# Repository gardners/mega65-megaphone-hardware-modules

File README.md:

# megaphone-r5-modular
Modularised MEGAphone Design

This project is being carried out with the support of the NLnet Foundation under: https://nlnet.nl/project/MEGA65-MVP/

The goal of this project is to push the MEGAphone forward towards a Minimum Viable Product (MVP) in a cost-effective way by modularising the PCB
allowing for faster development and lower development costs as a result. Also, the modularisation helps to work around supply-chain problems by
allowing the replacement of hard to source components, without requiring a full PCB redesign.  Those modules can also be manufactured much more easily
in a domestic setting, as there is less cumulative chance of messing something up.  Alternatively, they can be manufactured in modest sized batches
using PCB fabrication places like PCBWay, who also offer an assembly option.

The following sections outline the tasks and their current state of progress, where appropriate.

## Task 1: Development and testing of core simple cellular telephony and text messaging software

The software aspect of this project relates to the software required to control and interact with the hardware modules, as well as to perform basic telephony functionality.

## Task 2: Modularisation and testing of the PCB design

The major hardware stream of this project is focused on modularising the MEGAphone PCB, so that the modules can be iterated and/or manufactured independently. This is to support both users self-manufacturing, so that the complexity of the fabrication process can be greatly simplified, as well as to allow for much faster and, including ad-hoc response to future supply chain challenges. 

### 2.1 High-efficiency DC-DC converter module to power the various sub-systems

High-current and high-efficiency modules are required for the main FPGA, cellular modem, auxilliary communications module, LCD panel, and external speaker/bluetooth modules.  It is desirable to come up with a single module that can be reused several times for these purposes.  The cellular modems are likely to be the highest draw item, and according to https://ww1.microchip.com/downloads/en/Appnotes/ANLPS300-APID.pdf, they can draw upto around 2A at 3.3V, which is the voltage we will most likely use, since it allows a common voltage for many of our sub-systems.

It is unlikely that any other device on the system will consume more power than this, so our DC-DC modules need to support 2A.

A further requirement is that it must be buck-boost, as the LiFePO4 cells can go below 3.3V, but when charged are >3.3V.

Some possible parts to consider:

STBBJ3 https://www.st.com/en/power-management/stbb3j.html  (2A in buck mode, i.e., where VIN > 3.3V, but only 800mA in boost mode, i.e., where VIN < 3.3V). 5x4 grid array, without thermal pad. Shutdown and soft-start. "typical" efficiency of 94%
LTC3113 https://www.analog.com/media/en/technical-documentation/data-sheets/3113f.pdf (3A in buck mode, 1.5A in boost mode). "up to" 96% efficiency. Choice of grid array and TSSOP -- but with a concealled thermal pad on the underside, which is not easy to hand-solder. AU$20 each for TTSOP!

### 2.2 Low-energy power-management module to minimise energy consumption of device, especially in low-power modes

### 2.3 Battery management and energy harvesting module to allow USB-C, integrated solar panel and external 12/24V vehicle battery power sources, and efficient management of the integrated rechargeable battery

### 2.4 Cellular modem communications module, including SIM card module

### 2.5 Internal microphone and speaker module

### 2.6 External speaker and bluetooth headset interface module

### 2.7 Primary FPGA carrier module, leveraging off-the-shelf FPGA modules if at all possible

### 2.8 LCD panel interface module

### 2.9 Auxiliary communications module, e.g., LoRa, ultra-sonic, infra-red or mm wave

Low-cost LoRa devices based on the SX1262 look to be an option, using open-source software like this: https://github.com/beegee-tokyo/SX126x-Mesh-Network
The goal would be for the module to be able to autonomously participate in the mesh while the main process is off.  ESP32s can go into low power modes with <1mA consumption according to https://www.arrow.com/en/research-and-events/articles/esp32-power-consumption-can-be-reduced-with-sleep-modes, and the SX1262 uses only about 5mA to listen for packets, and perhaps 70mA when active, so this looks plausible. The SX1262 when transmitting can draw upto about 120mA according to https://semtech.my.salesforce.com/sfc/p/#E0000000JelG/a/2R000000Un7F/yT.fKdAr9ZAo3cJLc4F2cBdUsMftpT2vsOICP7NmvMo

Thus the total power consumption of an auxilliary communications module (assuming we include an ESP32 in it, rather than using the power management FPGA to run the mesh) will be about 5mA while idle (~17mW) and upto ~200mA (~660mW).

### 2.10 Main carrier board and assembly, into which the various modules connect

## Task 3: Integration, Integration testing and remediation of the modules

Once the modules have been tested independently, this activity is focussed on testing the behaviour of the modules when connected to one another, including any VHDL/FPGA programming required to achieve this.

### 3.1 Requirements specification and analysis

### 3.2 Hardware integration and testing, including FPGA programming

### 3.3 Software integration and testing

### 3.4 Engage with and respond to security and accessibility audits

### 3.5 Remediation and contingency – for addressing any issues with the software and/or hardware components identified during the integration, and implementing or documenting appropriate solutions and/or work-arounds as appropriate

## Task 4: Preparation of Prototype Units

This activity focuses on taking the integrated hardware and software modules, and building a small number of units that are alpha-quality prototypes.  The specific objective is that they be integrated into units that are suitable for developers to use to continue development of both hardware and software of the system.  These units may be somewhat larger than the final obtainable footprint, depending on the costs of designing and fabricating the housings/enclosures.  The limited budget prevents the engagement of industrial designers who would be required for the completion of design for manufacture. Instead, we anticipate that the enclosures will be relatively simple 3D printed designs.
The remediation budget line is to allow for adjustment to the case design, the fabricated case and/or any of the hardware modules, so that the prototypes can be assembled and be as functional as possible.

### 4.1 Case Design

### 4.2 Case Fabrication

### 4.3 Assembly

### 4.4 Remediation / Mitigation, e.g., of any fitment issues, whether by adjustment of the case, reworking of a module or other means.

Status of the modules 

| Milestone | Module | Reqs | Sch | Layout | Fab | Assembly | Test | Revision |
| --- | --- | --- | --- | --- | --- | --- | --- | --- |
| 2.1 | [High Efficieny DC-DC Converter](modules/high-efficiency_dc-dc_converter) | Y | Y | Y | Y | N | N | N |
| 2.2 | [Low-Enery Power Management Module]() | Y | Y | Y | Y | N | N | N |
| 2.3 | [Battery Management / Solar / Charge Module](modules/mppt-charge-controller) | Y | Y | Y | Y | N | N | N |
| 2.4 | [Cellular Modem Comms Module](modules/cellular-modem) | Y | Y | Y | Y | Y | Y | Y |
| 2.4 | [SIM Card Carrier](modules/sim-and-sd-card) | Y | Y | Y | Y | Y | Y | Y |
| 2.5 | [Internal microphone](modules/mems-microphone) | Y | N | N | N | N | N | N |
| 2.5 | [Internal speaker]() | Y | N | N | N | N | N | N |
| 2.6 | [External speaker]() | Y | Y | Y | Y | N | N | N |
| 2.6 | [Bluetooth headset interface](modules/bluetooth) | Y | N | N | N | N | N | N |
| 2.7 | [Primary FPGA carrier](modules/te0725-carrier) | Y | Y | Y | Y | N | N | N |
| 2.8 | [LCD Panel Interface](modules/lcd-panel) | Y | N | N | N | N | N | N |
| 2.9 | [Aux Comms]() | Y | N | N | N | N | N | N |
| 2.10 | [Main Carrier Board]() | Y | N | N | N | N | N | N |

### Assembled modules

First batch

LCD 

DC/DC

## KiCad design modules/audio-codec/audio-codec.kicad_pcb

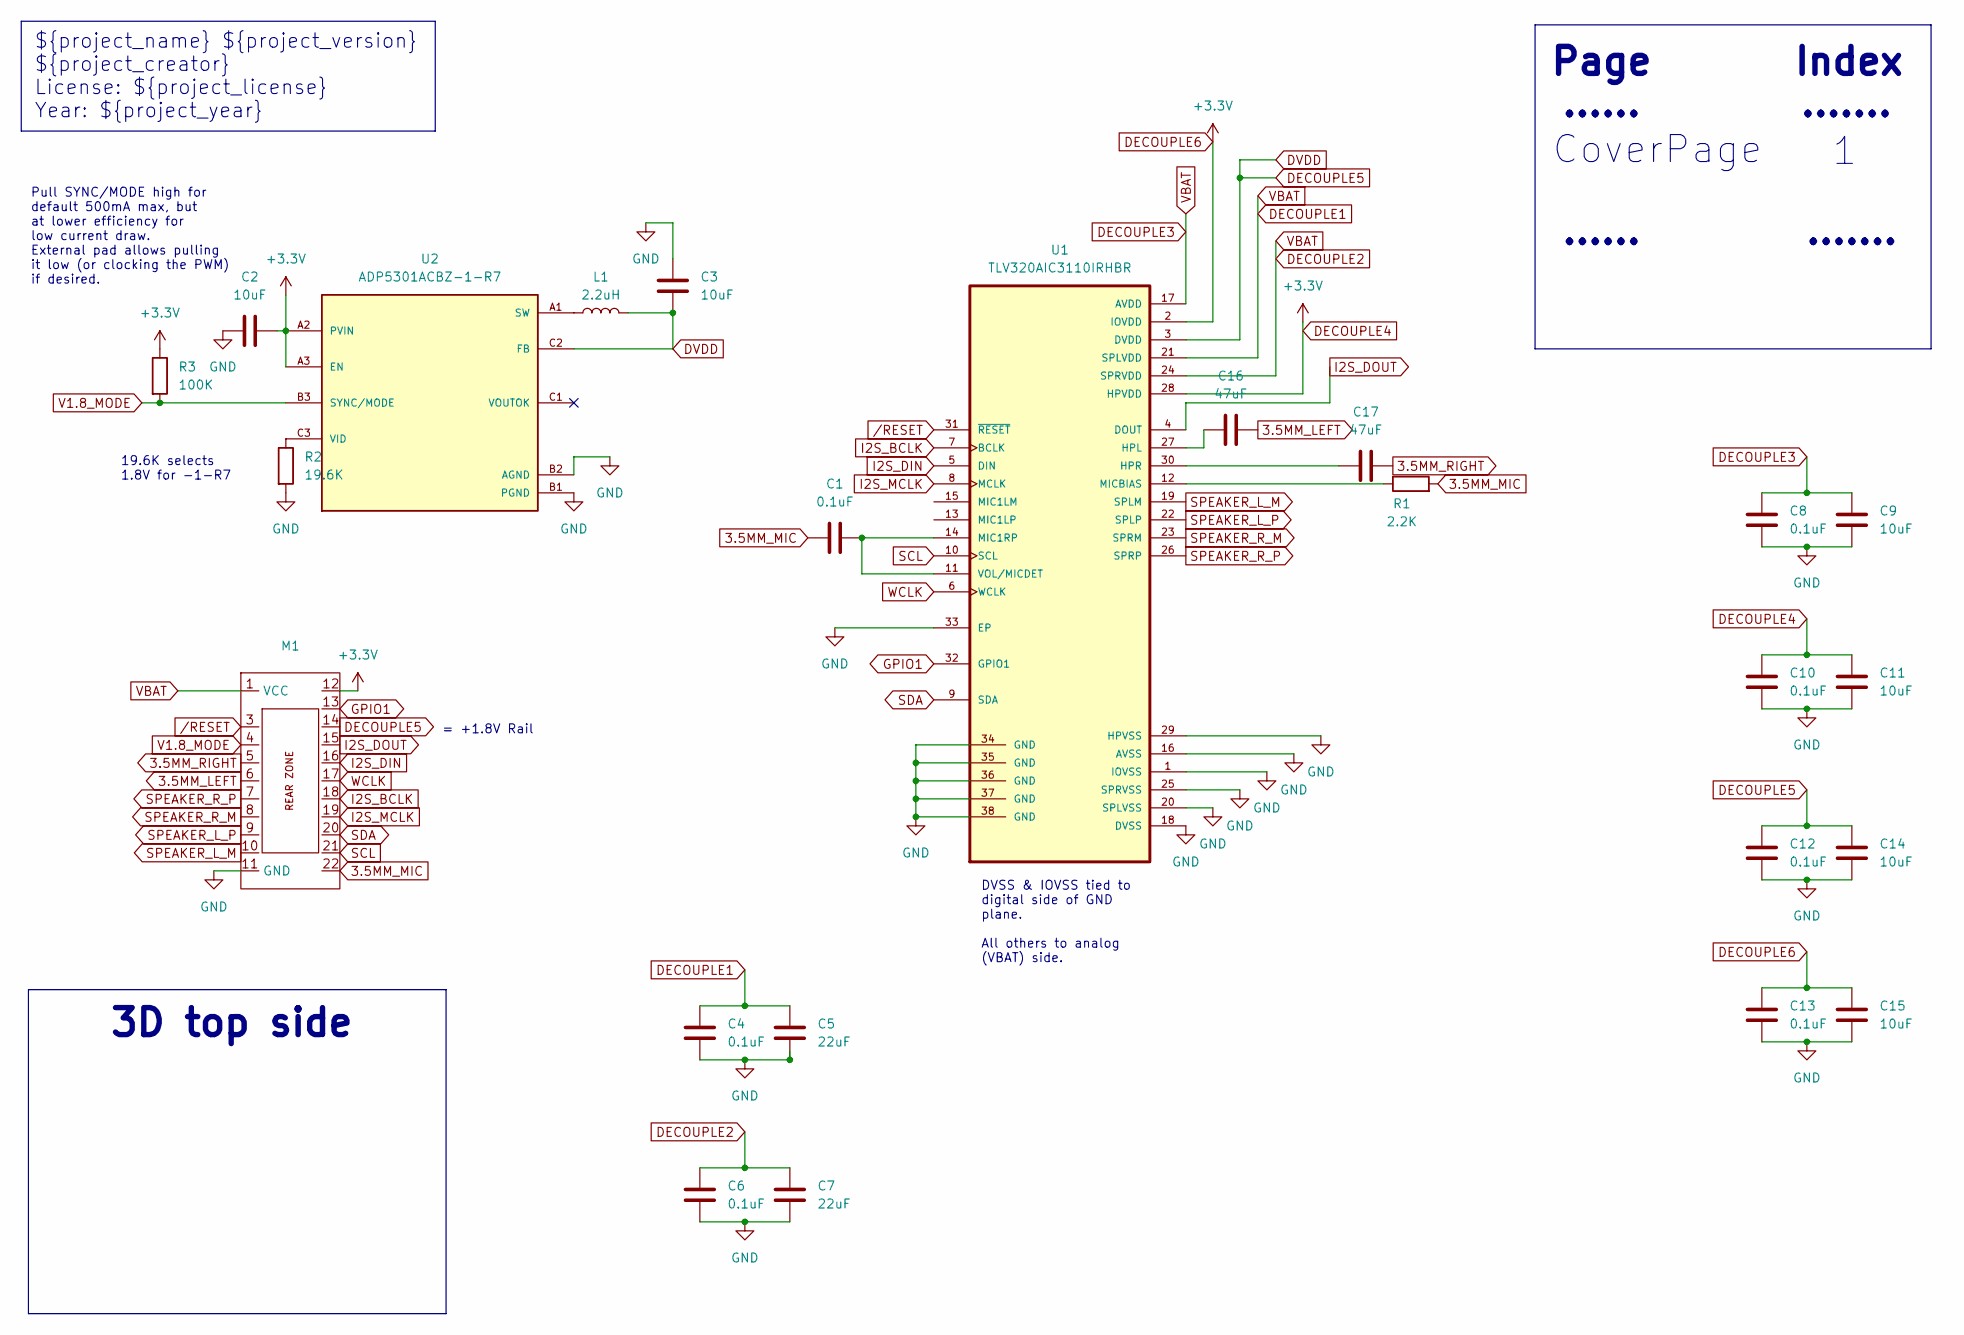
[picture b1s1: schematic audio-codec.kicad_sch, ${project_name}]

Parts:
C1, C4, C6, C8, C10, C12, C13: 0.1uF; C_0603_1608Metric; Mfr. PN C0603C104M4RAC; Mouser PN 80-C0603C104M4RAC
C2, C3, C9, C11, C14, C15: 10uF; C_0603_1608Metric; Mfr. PN C0603C106M9PAC7411; Mouser PN 80-C0603C106M9P7411
C5, C7: 22uF; C_0603_1608Metric; Mfr. PN CC0603MRX5R5BB226; Mouser PN 603-CC603MRX5R5BB226
C16, C17: 47uF; C_0603_1608Metric; Mfr. PN GRM188R60E476ME15J; Mouser PN 81-GRM188R60E476ME5J
L1: 2.2uH; L_0805_2012Metric; Mouser PN 810-MLP2016V2R2MT0S1
M1: MegaCastle2x11-Module-I22.0x23.1-MBFFFFC-SPAREPAD
R1: 2.2K; R_0603_1608Metric; Mfr. PN RT0603DRE072K2L; Mouser PN 603-RT0603DRE072K2L
R2: 19.6K; R_0603_1608Metric; Mouser PN 603-RT0603BRD0719K6L
R3: 100K; R_0603_1608Metric; Mouser PN 603-RC0603FR-07100KL
U1: TLV320AIC3110IRHBR; IC_ADS125H01IRHBT; Mouser PN 595-V320AIC3110IRHBR
U2: ADP5301ACBZ-1-R7; BGA9C50P3X3_187X165X66N; Mouser PN 584-ADP5301ACBZ-1-R7

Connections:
3.5MM_LEFT: C16.2, M1.6
3.5MM_MIC: C1.2, M1.22, R1.2
3.5MM_RIGHT: C17.2, M1.5
DECOUPLE1: C4.1, C5.1, C6.1, C7.1, C8.1, C9.1, M1.1 (VCC), U1.17 (AVDD), U1.21 (SPLVDD), U1.24 (SPRVDD)
DECOUPLE4: C2.2, C10.1, C11.1, C13.1, C15.1, M1.12, R3.1, U1.2 (IOVDD), U1.28 (HPVDD), U2.A2 (PVIN), U2.A3 (EN)
DECOUPLE5: C3.1, C12.1, C14.1, L1.2, M1.14, U1.3 (DVDD), U2.C2 (FB)
GND: C2.1, C3.2, C4.2, C5.2, C6.2, C7.2, C8.2, C9.2, C10.2, C11.2, C12.2, C13.2, C14.2, C15.2, M1.11 (GND), R2.2, U1.1 (IOVSS), U1.16 (AVSS), U1.18 (DVSS), U1.20 (SPLVSS), U1.25 (SPRVSS), U1.29 (HPVSS), U1.33 (EP), U1.34 (GND), U1.35 (GND), U1.36 (GND), U1.37 (GND), U1.38 (GND), U2.B1 (PGND), U2.B2 (AGND)
GPIO1: M1.13, U1.32 (GPIO1)
I2S_BCLK: M1.18, U1.7 (BCLK)
I2S_DIN: M1.16, U1.5 (DIN)
I2S_DOUT: M1.15, U1.4 (DOUT)
I2S_MCLK: M1.19, U1.8 (MCLK)
unnamed: C16.1, U1.27 (HPL)
unnamed: C17.1, U1.30 (HPR)
unnamed: C1.1, U1.11 (VOL/MICDET), U1.14 (MIC1RP)
unnamed: R1.1, U1.12 (MICBIAS)
unnamed: L1.1, U2.A1 (SW)
unnamed: R2.1, U2.C3 (VID)
SCL: M1.21, U1.10 (SCL)
SDA: M1.20, U1.9 (SDA)
SPEAKER_L_M: M1.10, U1.19 (SPLM)
SPEAKER_L_P: M1.9, U1.22 (SPLP)
SPEAKER_R_M: M1.8, U1.23 (SPRM)
SPEAKER_R_P: M1.7, U1.26 (SPRP)
V1.8_MODE: M1.4, R3.2, U2.B3 (SYNC/MODE)
WCLK: M1.17, U1.6 (WCLK)
/RESET: M1.3, U1.31 (~RESET)

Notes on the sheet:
Pull SYNC/MODE high for default 500mA max, but at lower efficiency for low current draw. External pad allows pulling it low (or clocking the PWM) if desired.
3D top side
......
CoverPage
19.6K selects 1.8V for -1-R7
${project_name} ${project_version} ${project_creator} License: ${project_license} Year: ${project_year}
Page
.......
= +1.8V Rail
DVSS & IOVSS tied to digital side of GND plane. All others to analog (VBAT) side.
Index

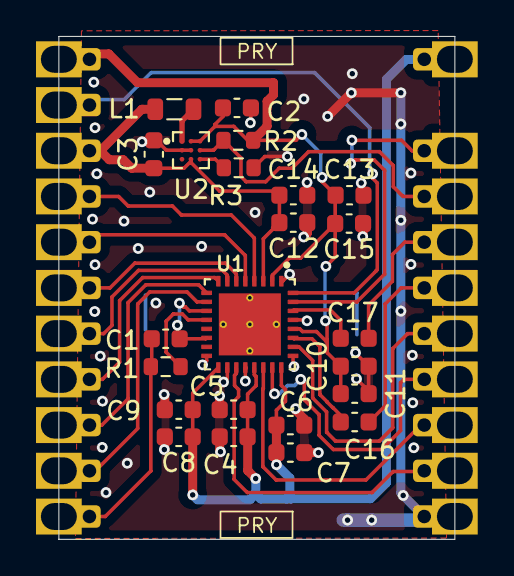
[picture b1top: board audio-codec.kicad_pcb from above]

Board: 2 copper layers, 22.0 x 27.9 mm, 24 parts (1 on the bottom side), 27 nets.

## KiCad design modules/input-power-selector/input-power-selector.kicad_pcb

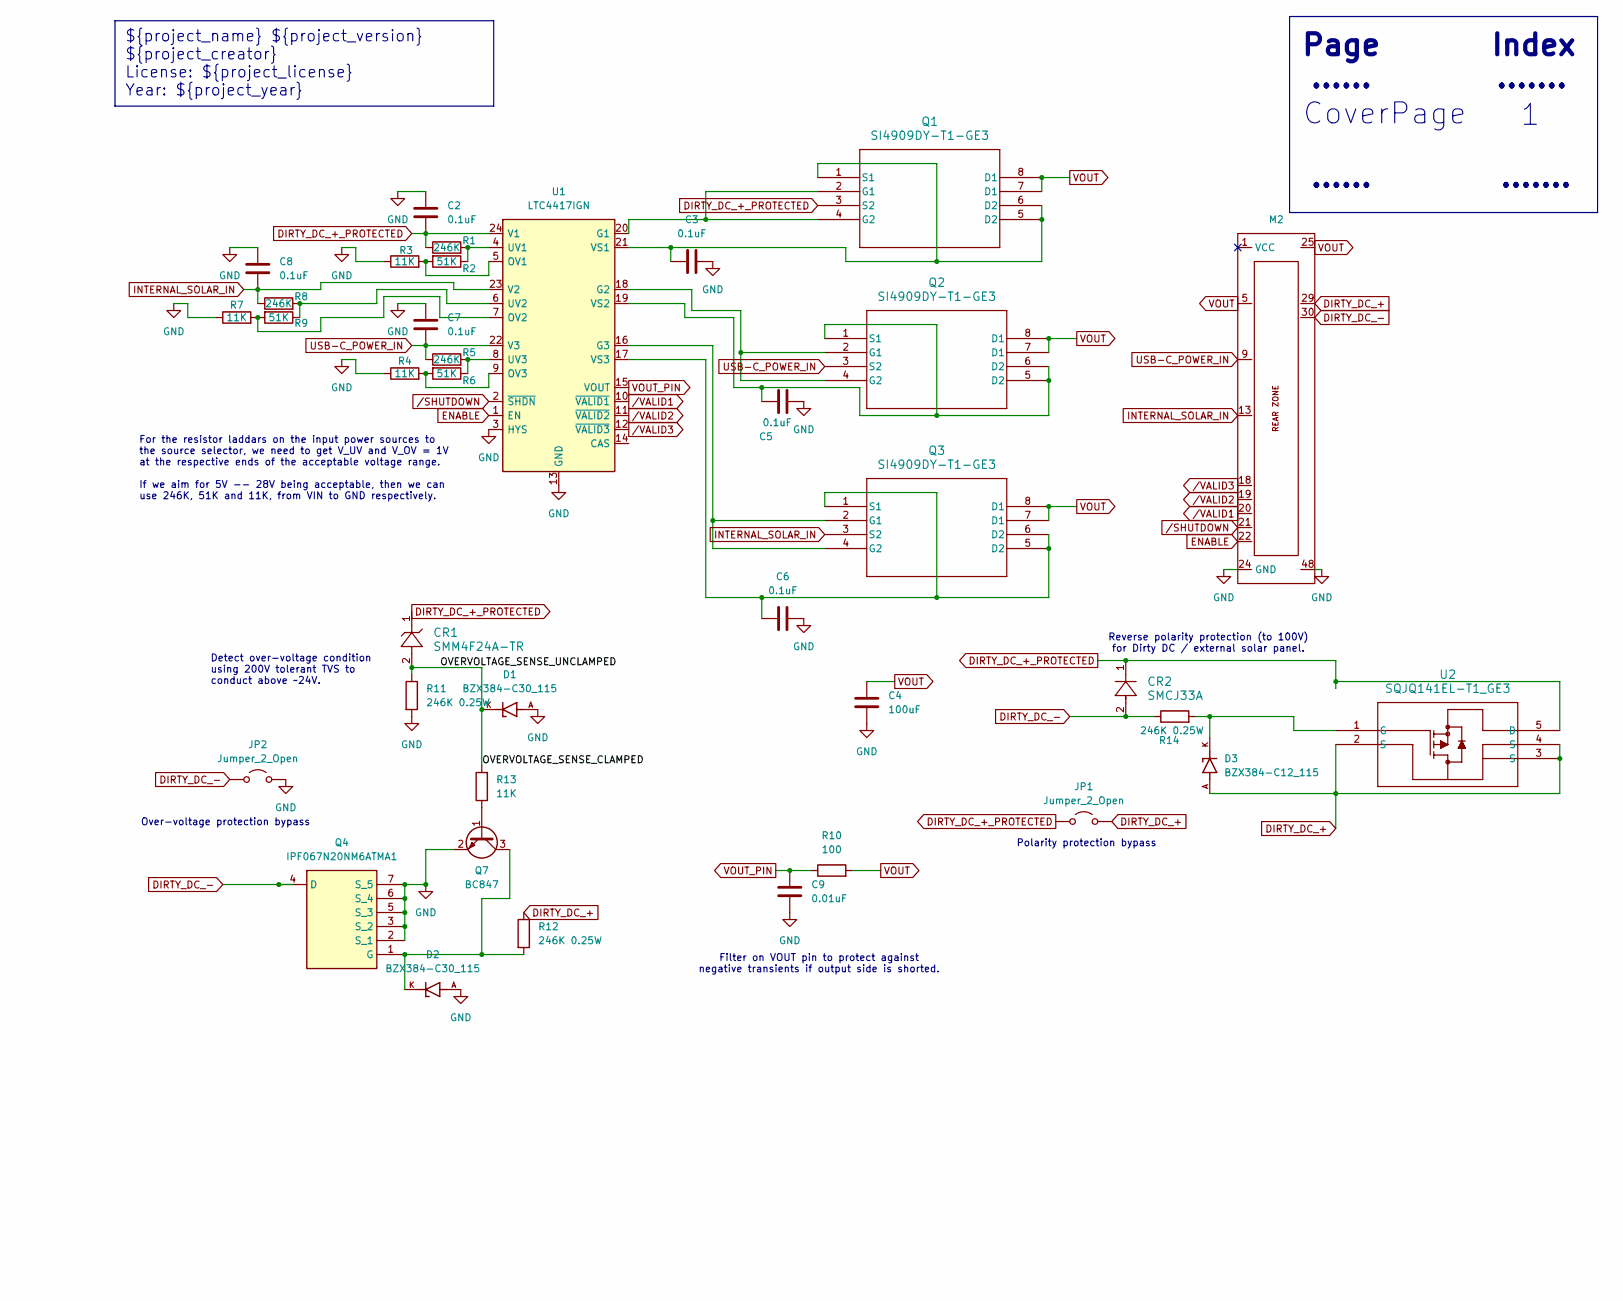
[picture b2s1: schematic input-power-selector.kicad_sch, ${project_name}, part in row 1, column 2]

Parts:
C2, C3, C5, C6, C7, C8: 0.1uF; C_0805_2012Metric; Manufacturer_Part_Number 0805DC104MAT2A; Mouser Part Number 581-0805DC104MAT2A
C4: 100uF; C_0805_2012Metric
C9: 0.01uF; C_0805_2012Metric
CR1: SMM4F24A-TR; Manufacturer_Part_Number SMM4F24A-TR; Mouser Part Number 511-SMM4F24A-TR
CR2: SMCJ33A; Manufacturer_Part_Number 652-SMCJ33A; Mouser Part Number SMCJ33A
D1, D2: BZX384-C30_115; DIO_BZX384-C30_115; Manufacturer_Part_Number BZX384-C30,115; Mouser Part Number 771-BZX384-C30115
D3: BZX384-C12_115; DIO_BZX384-C30_115; Manufacturer_Part_Number BZX384-C12,115; Mouser Part Number 771-BZX384-C12115
JP1, JP2: Jumper_2_Open; SolderJumper-2_P1.3mm_Open_RoundedPad1.0x1.5mm
M2: MegaCastle2x24-Module-I47.0x56.2-M88887D8C0001-SPAREPAD
Q1, Q2, Q3: SI4909DY-T1-GE3; Manufacturer_Part_Number SI4909DY-T1-GE3; Mouser Part Number 78-SI4909DY-T1-GE3
Q4: IPF067N20NM6ATMA1; Mouser Part Number 726-IPF067N20NM6ATMA
Q7: BC847; SOT-23; Manufacturer_Part_Number 637-BC847B; Mouser Part Number BC847B
R1, R5, R8: 246K; R_0805_2012Metric
R2, R6, R9: 51K; R_0805_2012Metric; Manufacturer_Part_Number RV0805FR-0751KL; Mouser Part Number 603-RV0805FR-0751KL
R3, R4, R7, R13: 11K; R_0805_2012Metric; Manufacturer_Part_Number RT0805DRE0711KL; Mouser Part Number 603-RT0805DRE0711KL
R10: 100; R_0805_2012Metric; Manufacturer_Part_Number PCF0805R-100RBI; Mouser Part Number 756-PCF0805R100RBI
R11, R12, R14: 246K 0.25W; R_0805_2012Metric; Manufacturer_Part_Number PTN0805E2463BST1; Mouser Part Number 71-PTN0805E2463BST1
U1: LTC4417IGN; SSOP-24_3.9x8.7mm_P0.635mm; Manufacturer_Part_Number LTC4417IGN#PBF; Mouser Part Number 584-LTC4417IGN#PBF
U2: SQJQ141EL-T1_GE3; SOT95P280X120-6N; Manufacturer_Part_Number SQJQ141EL-T1_GE3; Mouser Part Number 78-SQJQ141EL-T1_GE3

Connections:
/OVERVOLTAGE_SENSE_CLAMPED: CR1.2, D1.K, R11.1, R13.2
DIRTY_DC_+: D3.A, JP1.2 (B), M2.29, R12.1, U2.2 (S), U2.3 (S), U2.4 (S)
DIRTY_DC_+_PROTECTED: C2.2, CR1.1, CR2.1, JP1.1 (A), Q1.3 (S2), R1.1, U1.24 (V1), U2.5 (D)
DIRTY_DC_-: CR2.2, JP2.1 (A), M2.30, Q4.4 (D), R14.1
ENABLE: M2.22, U1.1 (EN)
GND: C2.1, C3.2, C4.2, C5.2, C6.2, C7.1, C8.1, C9.2, D1.A, D2.A, JP2.2 (B), M2.24 (GND), M2.48, Q4.2 (S_1), Q4.3 (S_2), Q4.5 (S_3), Q4.6 (S_4), Q4.7 (S_5), Q7.2 (E), R3.1, R4.1, R7.1, R11.2, U1.3 (HYS), U1.13 (GND)
INTERNAL_SOLAR_IN: C8.2, M2.13, Q3.3 (S2), R8.1, U1.23 (V2)
unnamed: Q1.2 (G1), Q1.4 (G2), U1.20 (G1)
unnamed: C3.1, Q1.1 (S1), Q1.5 (D2), Q1.6 (D2), U1.21 (VS1)
unnamed: Q2.2 (G1), Q2.4 (G2), U1.18 (G2)
unnamed: C5.1, Q2.1 (S1), Q2.5 (D2), Q2.6 (D2), U1.19 (VS2)
unnamed: Q3.2 (G1), Q3.4 (G2), U1.16 (G3)
unnamed: C6.1, Q3.1 (S1), Q3.5 (D2), Q3.6 (D2), U1.17 (VS3)
unnamed: D2.K, Q4.1 (G), Q7.3 (C), R12.2
unnamed: Q7.1 (B), R13.1
unnamed: R2.2, R3.2, U1.5 (OV1)
unnamed: R7.2, R9.2, U1.7 (OV2)
unnamed: R4.2, R6.2, U1.9 (OV3)
unnamed: R1.2, R2.1, U1.4 (UV1)
unnamed: R8.2, R9.1, U1.6 (UV2)
unnamed: R5.2, R6.1, U1.8 (UV3)
unnamed: D3.K, R14.2, U2.1 (G)
USB-C_POWER_IN: C7.2, M2.9, Q2.3 (S2), R5.1, U1.22 (V3)
VOUT: C4.1, M2.5, M2.25, Q1.7 (D1), Q1.8 (D1), Q2.7 (D1), Q2.8 (D1), Q3.7 (D1), Q3.8 (D1), R10.2
VOUT_PIN: C9.1, R10.1, U1.15 (VOUT)
/SHUTDOWN: M2.21, U1.2 (~SHDN)
/VALID1: M2.20, U1.10 (~VALID1)
/VALID2: M2.19, U1.11 (~VALID2)
/VALID3: M2.18, U1.12 (~VALID3)

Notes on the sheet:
For the resistor laddars on the input power sources to the source selector, we need to get V_UV and V_OV = 1V at the respective ends of the acceptable voltage range. If we aim for 5V -- 28V being acceptable, then we can use 246K, 51K and 11K, from VIN to GND respectively.
3D top side
Filter on VOUT pin to protect against negative transients if output side is shorted.
......
CoverPage
Reverse polarity protection (to 100V) for Dirty DC / external solar panel.
${project_name} ${project_version} ${project_creator} License: ${project_license} Year: ${project_year}
Page
.......
Index
Over-voltage protection bypass
Detect over-voltage condition using 200V tolerant TVS to conduct above ~24V.
Polarity protection bypass

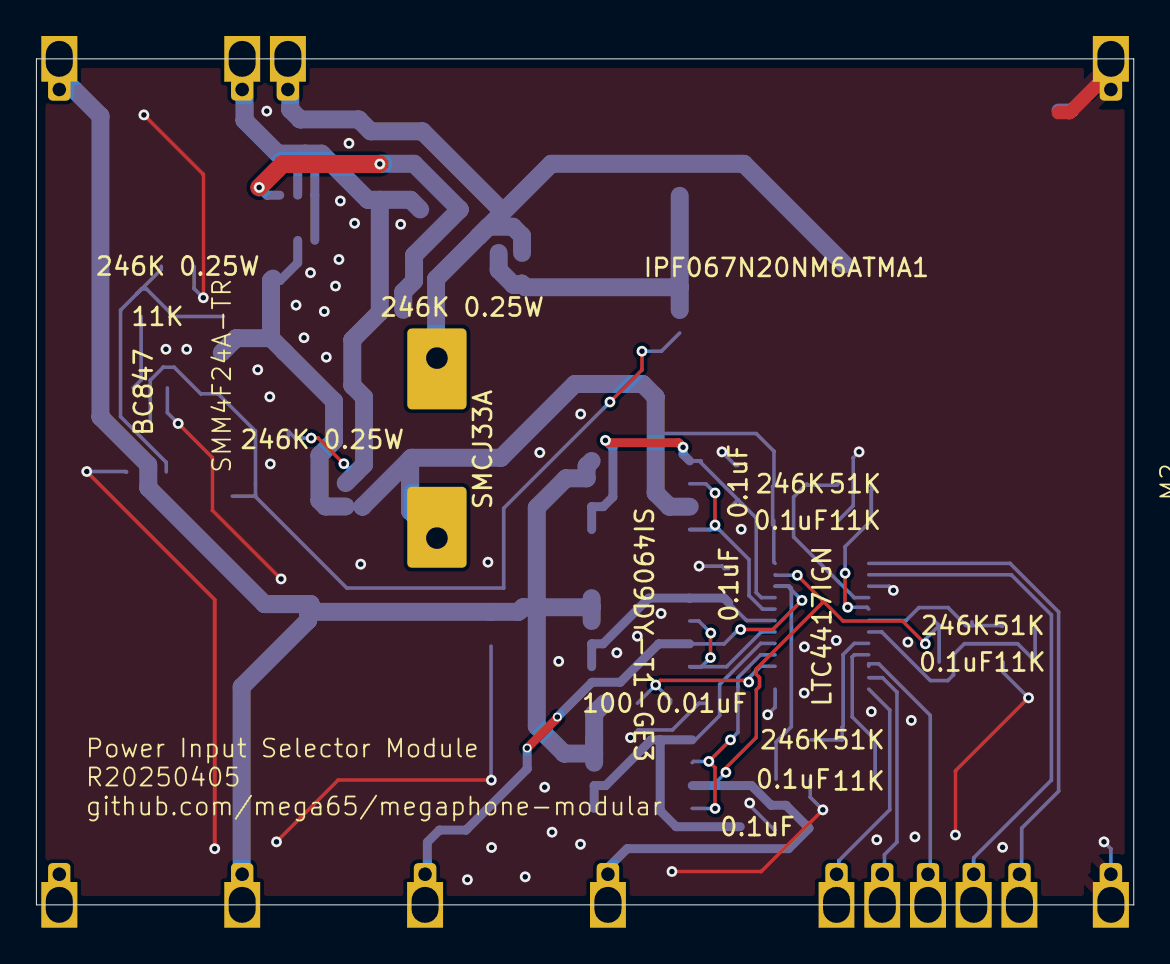
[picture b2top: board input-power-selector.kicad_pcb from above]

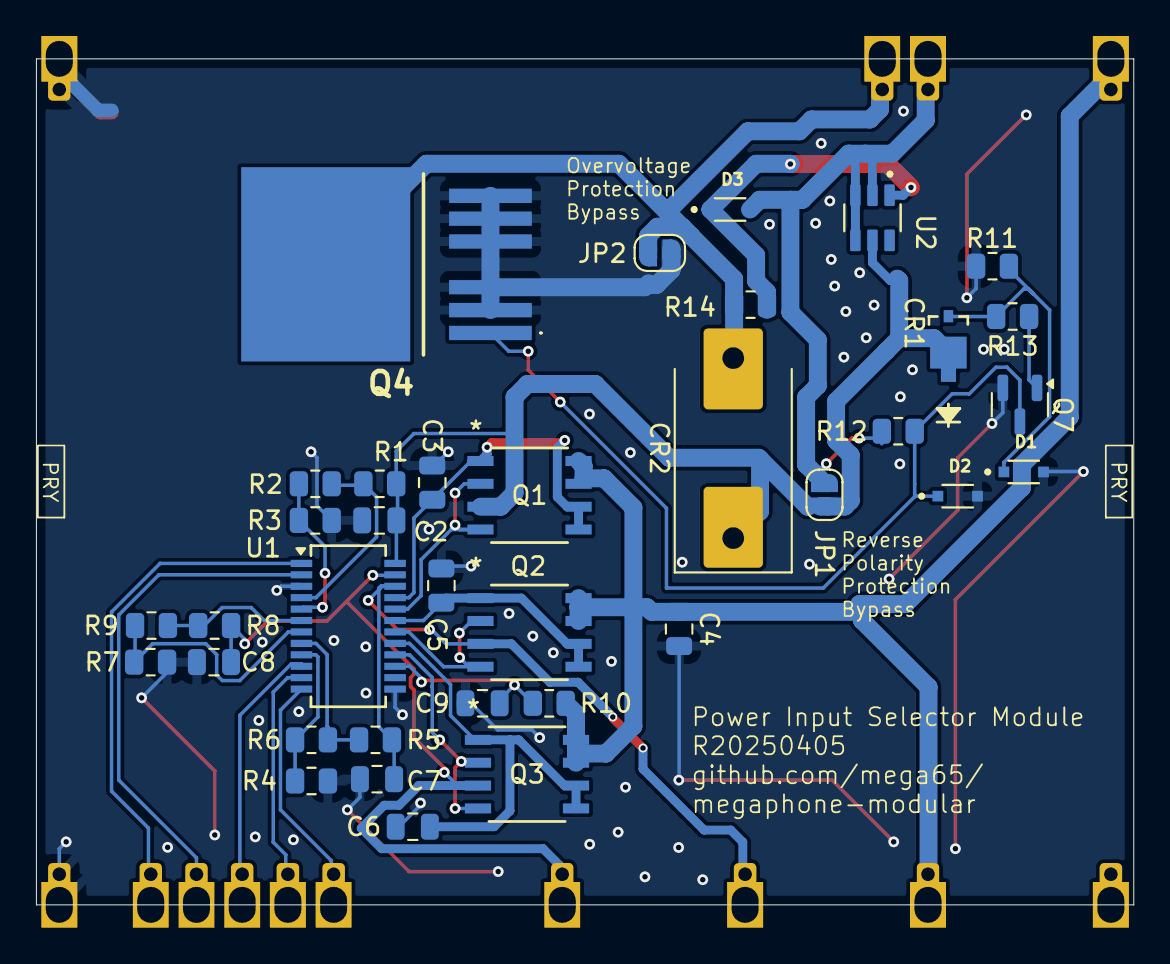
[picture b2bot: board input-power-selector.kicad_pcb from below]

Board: 2 copper layers, 61.0 x 47.0 mm, 37 parts (36 on the bottom side), 29 nets.

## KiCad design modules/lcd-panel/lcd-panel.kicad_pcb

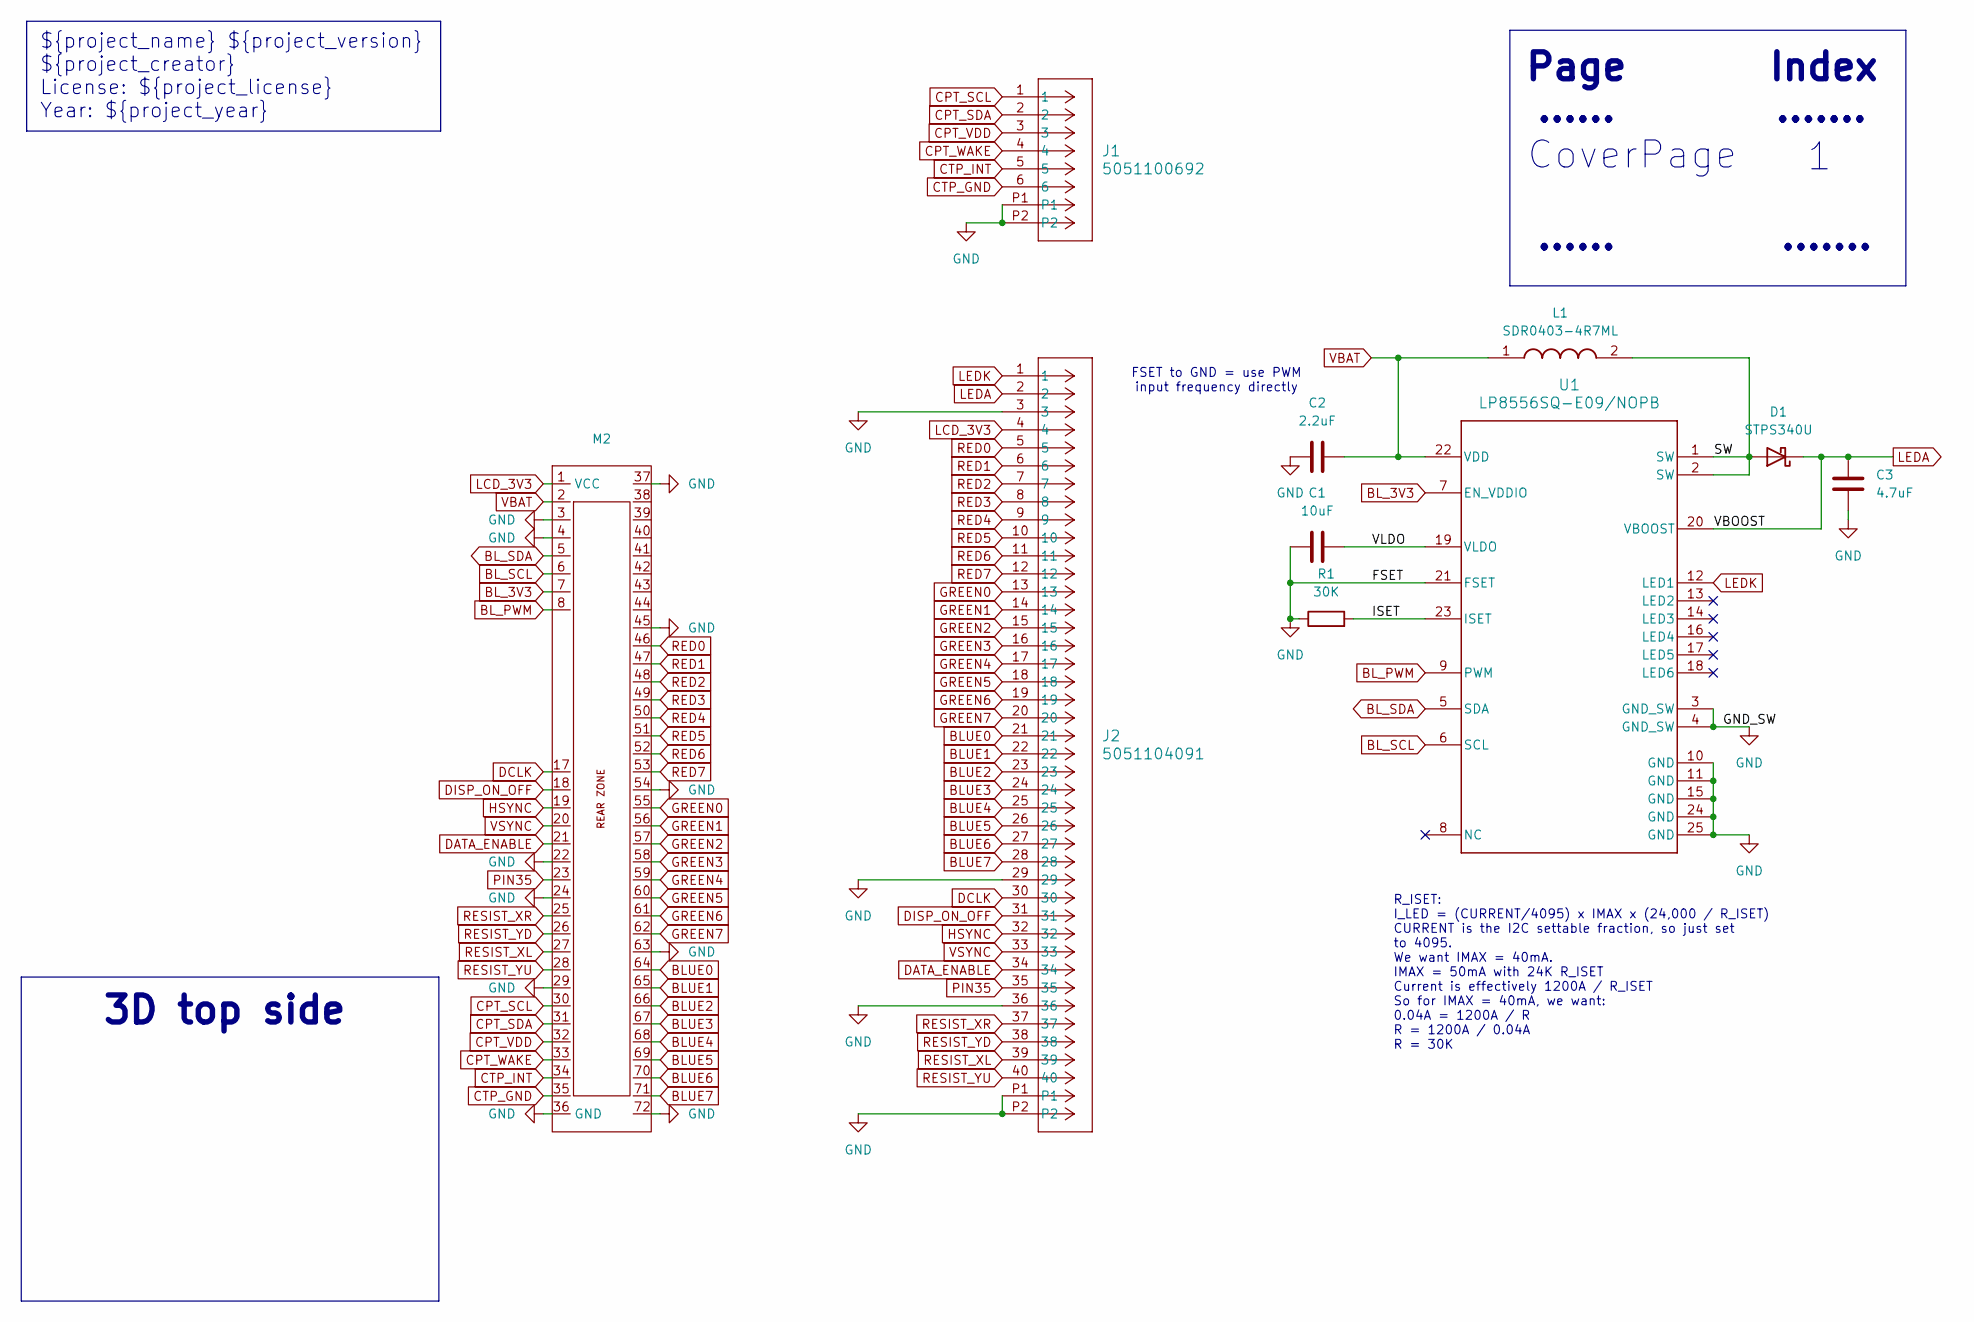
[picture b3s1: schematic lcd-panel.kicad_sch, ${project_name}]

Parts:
C1: 10uF; C_0603_1608Metric_Pad1.08x0.95mm_HandSolder
C2: 2.2uF; C_0603_1608Metric_Pad1.08x0.95mm_HandSolder
C3: 4.7uF; C_0603_1608Metric_Pad1.08x0.95mm_HandSolder
D1: STPS340U; D_SOD-123
J1: 5051100692; CON_5051100692_MOL
J2: 5051104091; CON_5051104091_MOL
L1: SDR0403-4R7ML; SDR0403; Mouser Part Number 652-SDR0403-4R7ML
M2: MegaCastle2x36-Module-I40.0x86.6-MFFFFFFFFFFFFFF-SPAREPAD
R1: 30K; R_0603_1608Metric_Pad0.98x0.95mm_HandSolder
U1: LP8556SQ-E09/NOPB; RTW0024A

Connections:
/ISET: R1.2, U1.23 (ISET)
/SW: D1.2 (A), L1.2, U1.1 (SW), U1.2 (SW)
/VLDO: C1.2, U1.19 (VLDO)
BLUE0: J2.21, M2.64
BLUE1: J2.22, M2.65
BLUE2: J2.23, M2.66
BLUE3: J2.24, M2.67
BLUE4: J2.25, M2.68
BLUE5: J2.26, M2.69
BLUE6: J2.27, M2.70
BLUE7: J2.28, M2.71
BL_3V3: M2.7, U1.7 (EN_VDDIO)
BL_PWM: M2.8, U1.9 (PWM)
BL_SCL: M2.6, U1.6 (SCL)
BL_SDA: M2.5, U1.5 (SDA)
CPT_SCL: J1.1, M2.30
CPT_SDA: J1.2, M2.31
CPT_VDD: J1.3, M2.32
CPT_WAKE: J1.4, M2.33
CTP_GND: J1.6, M2.35
CTP_INT: J1.5, M2.34
DATA_ENABLE: J2.34, M2.21
DCLK: J2.30, M2.17
DISP_ON_OFF: J2.31, M2.18
GND: C1.1, C2.1, C3.2, J1.P1, J1.P2, J2.3, J2.29, J2.36, J2.P1, J2.P2, M2.3, M2.4, M2.22, M2.24, M2.29, M2.36 (GND), M2.37, M2.45, M2.54, M2.63, M2.72, R1.1, U1.3 (GND_SW), U1.4 (GND_SW), U1.10 (GND), U1.11 (GND), U1.15 (GND), U1.21 (FSET), U1.24 (GND), U1.25 (GND)
GREEN0: J2.13, M2.55
GREEN1: J2.14, M2.56
GREEN2: J2.15, M2.57
GREEN3: J2.16, M2.58
GREEN4: J2.17, M2.59
GREEN5: J2.18, M2.60
GREEN6: J2.19, M2.61
GREEN7: J2.20, M2.62
HSYNC: J2.32, M2.19
LCD_3V3: J2.4, M2.1 (VCC)
LEDA: C3.1, D1.1 (K), J2.2, U1.20 (VBOOST)
LEDK: J2.1, U1.12 (LED1)
PIN35: J2.35, M2.23
RED0: J2.5, M2.46
RED1: J2.6, M2.47
RED2: J2.7, M2.48
RED3: J2.8, M2.49
RED4: J2.9, M2.50
RED5: J2.10, M2.51
RED6: J2.11, M2.52
RED7: J2.12, M2.53
RESIST_XL: J2.39, M2.27
RESIST_XR: J2.37, M2.25
RESIST_YD: J2.38, M2.26
RESIST_YU: J2.40, M2.28
VBAT: C2.2, L1.1, M2.2, U1.22 (VDD)
VSYNC: J2.33, M2.20

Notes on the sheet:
3D top side
......
CoverPage
FSET to GND = use PWM input frequency directly
${project_name} ${project_version} ${project_creator} License: ${project_license} Year: ${project_year}
Page
.......
Index
R_ISET: I_LED = (CURRENT/4095) x IMAX x (24,000 / R_ISET) CURRENT is the I2C settable fraction, so just set to 4095. We want IMAX = 40mA. IMAX = 50mA with 24K R_ISET Current is effectively 1200A / R_ISET So for IMAX = 40mA, we want: 0.04A = 1200A / R R = 1200A / 0.04A R = 30K

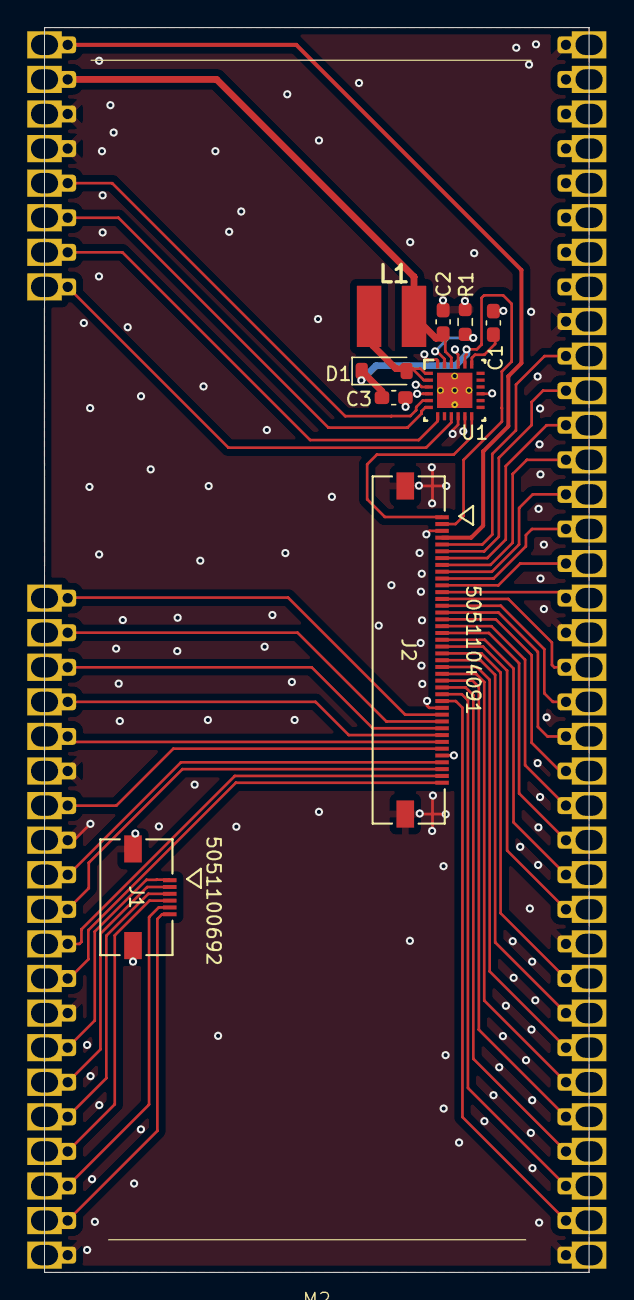
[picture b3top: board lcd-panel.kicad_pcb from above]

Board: 4 copper layers, 40.0 x 91.4 mm, 10 parts (0 on the bottom side), 52 nets.

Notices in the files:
modules/mppt-charge/mppt-charge.kicad_pcb:
${TITLE} r20250219 GPLv3
parts and their libraries:
project_license: CERN-OHL-S v2
